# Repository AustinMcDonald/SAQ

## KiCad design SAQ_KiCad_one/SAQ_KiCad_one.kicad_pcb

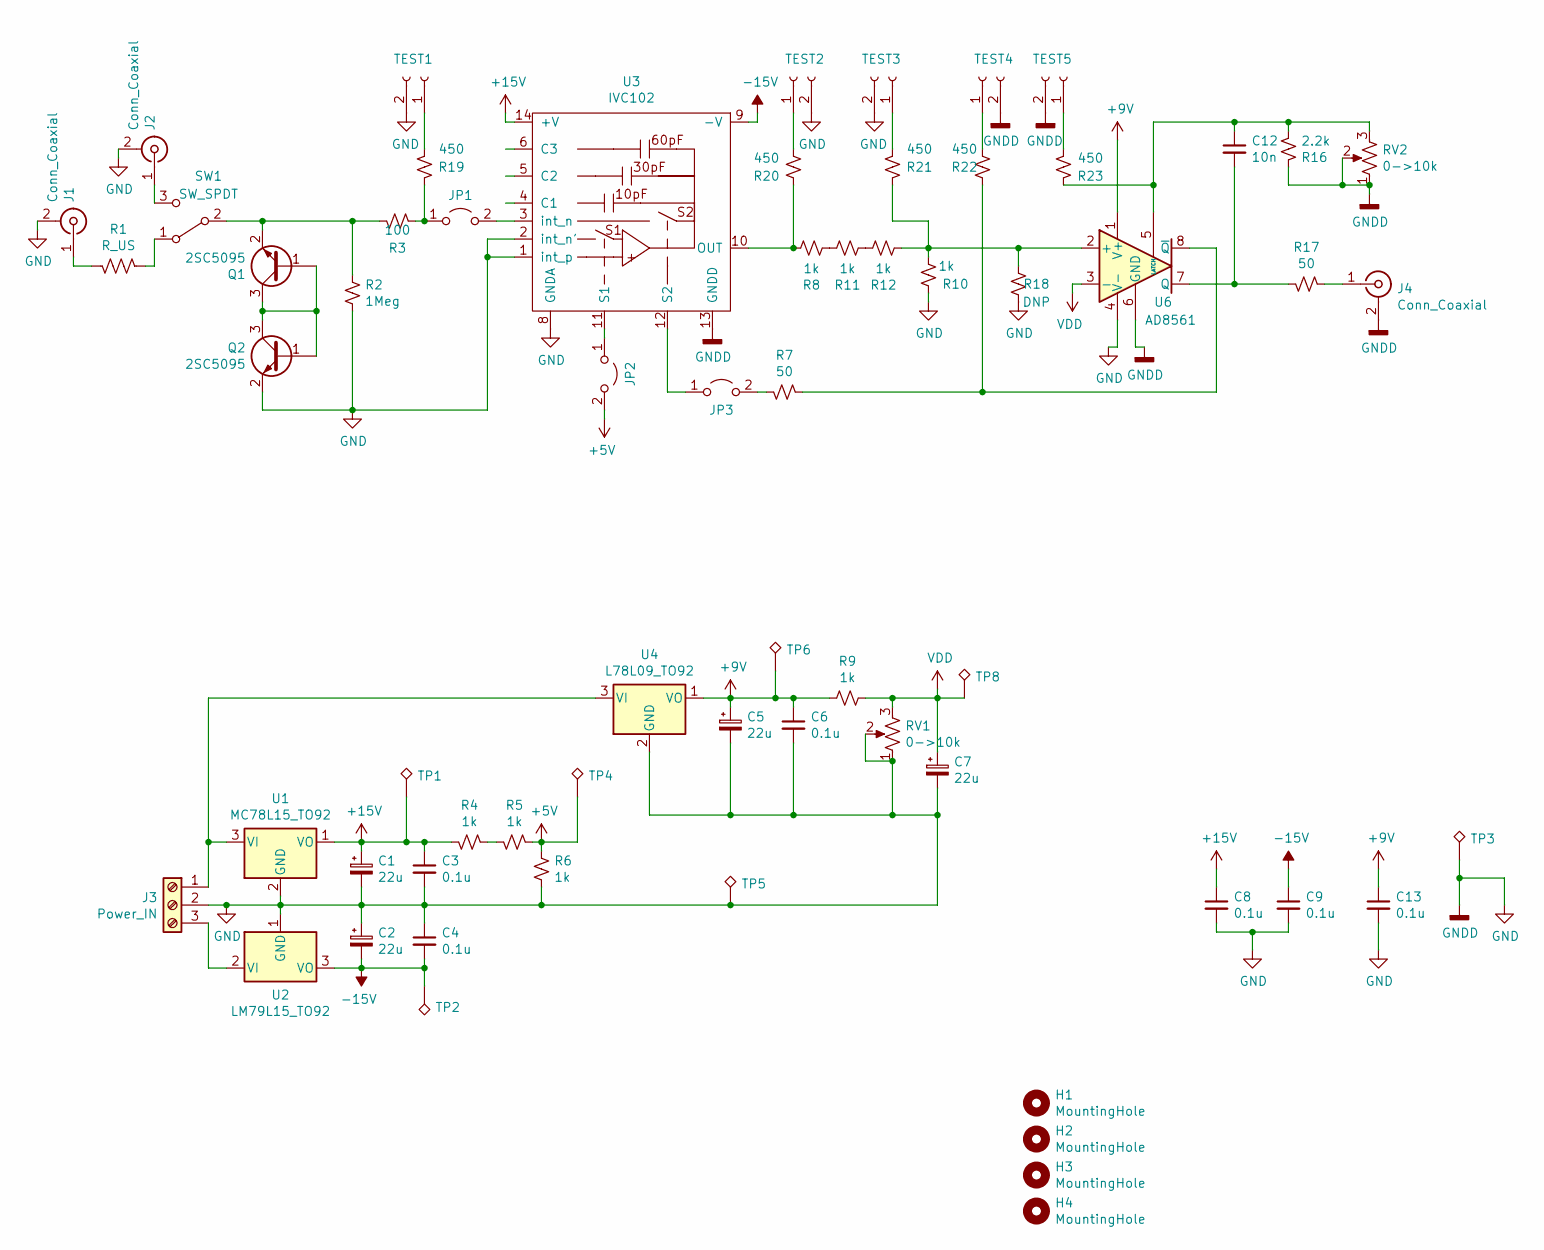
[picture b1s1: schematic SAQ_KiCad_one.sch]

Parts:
C1, C2, C5, C7: 22u; CP_Elec_5x5.3
C3, C4, C6, C8, C9, C13: 0.1u; C_1206_3216Metric_Pad1.33x1.80mm_HandSolder
C12: 10n; C_1206_3216Metric_Pad1.33x1.80mm_HandSolder
H1, H2, H3, H4: MountingHole; MountingHole_3.2mm_M3_DIN965
J1, J2, J4: Conn_Coaxial; SMA_Amphenol_132134_Vertical
J3: Power_IN; TerminalBlock_MetzConnect_Type055_RT01503HDWU_1x03_P5.00mm_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
JP1: Jumper_2_Open; R_Axial_DIN0204_L3.6mm_D1.6mm_P2.54mm_Vertical
JP2, JP3: Jumper_2_Open; SolderJumper-2_P1.3mm_Open_RoundedPad1.0x1.5mm
Q1, Q2: 2SC5095; SOT-23
R1: R_US; R_Axial_DIN0204_L3.6mm_D1.6mm_P7.62mm_Horizontal
R2: 1Meg; R_0805_2012Metric_Pad1.20x1.40mm_HandSolder
R3: 100; R_0805_2012Metric_Pad1.20x1.40mm_HandSolder
R4, R5, R6, R8, R9, R10, R11, R12: 1k; R_0805_2012Metric_Pad1.20x1.40mm_HandSolder
R7, R17: 50; R_0805_2012Metric_Pad1.20x1.40mm_HandSolder
R16: 2.2k; R_0805_2012Metric_Pad1.20x1.40mm_HandSolder
R18: DNP; R_0805_2012Metric_Pad1.20x1.40mm_HandSolder
R19, R20, R21, R22, R23: 450; R_0805_2012Metric_Pad1.20x1.40mm_HandSolder
RV1, RV2: 0->10k; Potentiometer_Bourns_3214W_Vertical
SW1: SW_SPDT; SW_Slide_1P2T_CK_OS102011MS2Q
TEST1, TEST2, TEST3, TEST4, TEST5: Conn_01x02_Female; PinSocket_1x02_P2.54mm_Vertical
TP1, TP2, TP4, TP6, TP8: TestPoint_Alt; TestPoint_THTPad_2.5x2.5mm_Drill1.2mm
TP3, TP5: TestPoint_Alt; TestPoint_THTPad_D4.0mm_Drill2.0mm
U1: MC78L15_TO92; TO-92_Inline
U2: LM79L15_TO92; TO-92_Inline
U3: IVC102; SOIC-14_3.9x8.7mm_P1.27mm
U4: L78L09_TO92; TO-92_Inline
U6: AD8561; SOIC-8_3.9x4.9mm_P1.27mm

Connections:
+5V: JP2.2 (B), R5.2, R6.1, TP4.1
+9V: C5.1, C6.1, C13.1, R9.2, TP6.1, U4.1 (VO), U6.1 (V+)
+15V: C1.1, C3.1, C8.1, R4.1, TP1.1, U1.1 (VO), U3.14 (+V)
-15V: C2.2, C4.2, C9.1, TP2.1, U2.3 (VO), U3.9 (-V)
GND: C1.2, C2.1, C3.2, C4.1, C5.2, C6.2, C7.2, C8.2, C9.2, C13.2, J1.2 (Ext), J2.2 (Ext), J3.2, J4.2 (Ext), Q2.2 (E), R2.1, R6.2, R10.1, R16.2, R18.2, RV1.1, RV1.2, RV2.1, RV2.2, TEST1.2, TEST2.2, TEST3.2, TEST4.2, TEST5.2, TP3.1, TP5.1, U1.2 (GND), U2.1 (GND), U3.1 (int_p), U3.2 (int_n'), U3.7 (nc), U3.8 (GNDA), U3.13 (GNDD), U4.2 (GND), U6.4 (V-), U6.6 (GND)
unnamed: C12.1, R16.1, R23.2, RV2.3, U6.5 (LATCH)
unnamed: C12.2, R17.1, U6.7 (Q)
unnamed: J1.1 (In), R1.2
unnamed: J2.1 (In), SW1.3 (C)
unnamed: J3.1, U1.3 (VI), U4.3 (VI)
unnamed: J3.3, U2.2 (VI)
unnamed: J4.1 (In), R17.2
unnamed: JP1.1 (A), R3.2, R19.2
unnamed: JP1.2 (B), U3.3 (int_n)
unnamed: JP2.1 (A), U3.11 (S1)
unnamed: JP3.1 (A), U3.12 (S2)
unnamed: JP3.2 (B), R7.1
unnamed: Q1.1 (B), Q1.3 (C), Q2.1 (B), Q2.3 (C)
unnamed: Q1.2 (E), R2.2, R3.1, SW1.2 (B)
unnamed: R1.1, SW1.1 (A)
unnamed: R4.2, R5.1
unnamed: R10.2, R12.2, R18.1, R21.2, U6.2 (+)
unnamed: R8.2, R11.1
unnamed: R11.2, R12.1
unnamed: R19.1, TEST1.1
unnamed: R20.1, TEST2.1
unnamed: R8.1, R20.2, U3.10 (OUT)
unnamed: R21.1, TEST3.1
unnamed: R22.1, TEST4.1
unnamed: R7.2, R22.2, U6.8 (~Q)
unnamed: R23.1, TEST5.1
VDD: C7.1, R9.1, RV1.3, TP8.1, U6.3 (-)

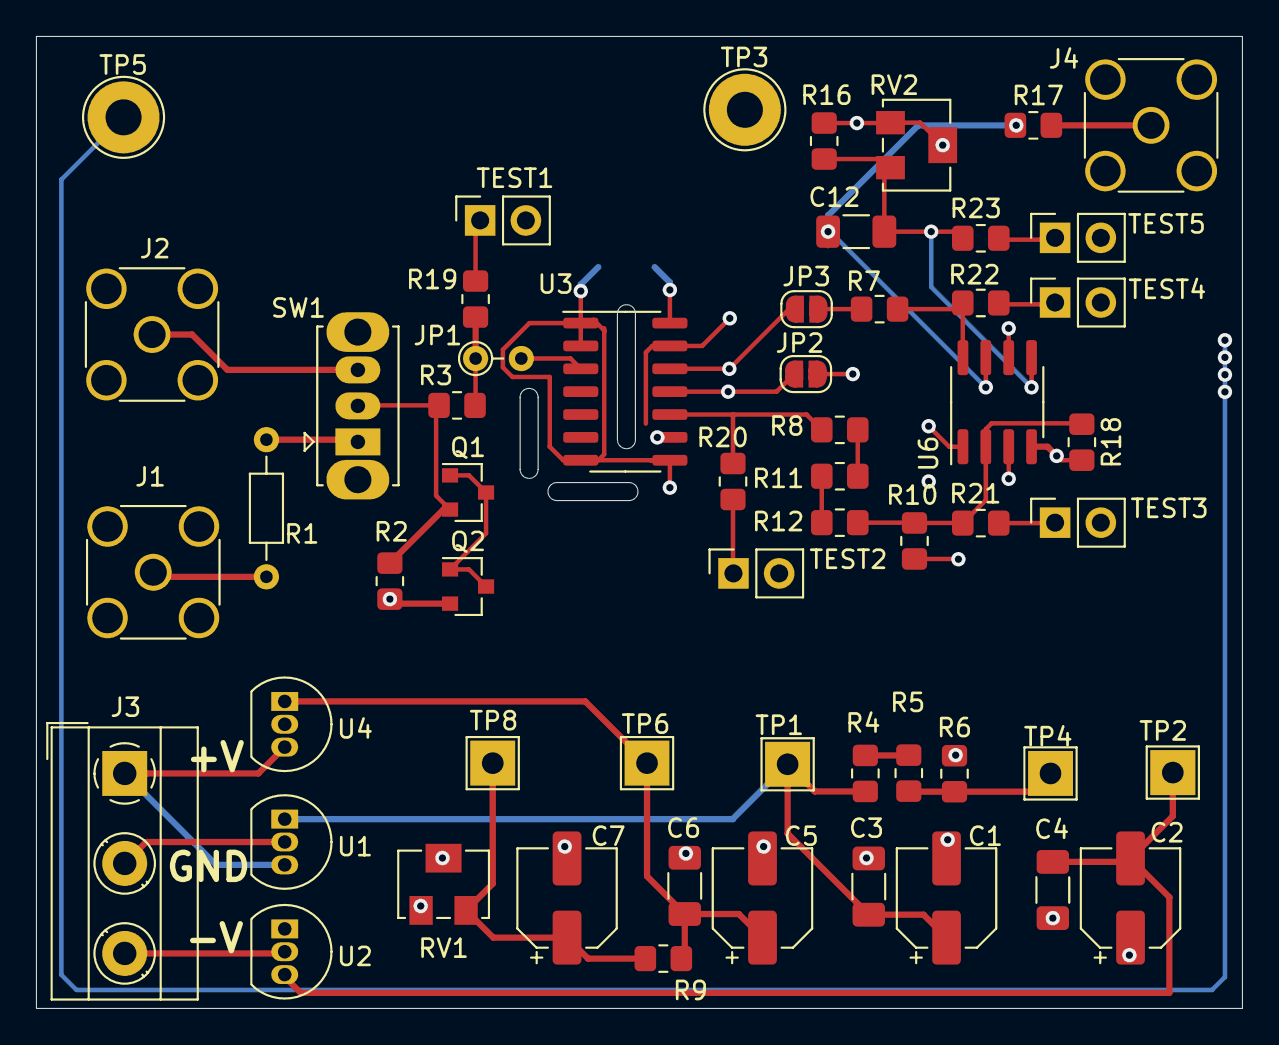
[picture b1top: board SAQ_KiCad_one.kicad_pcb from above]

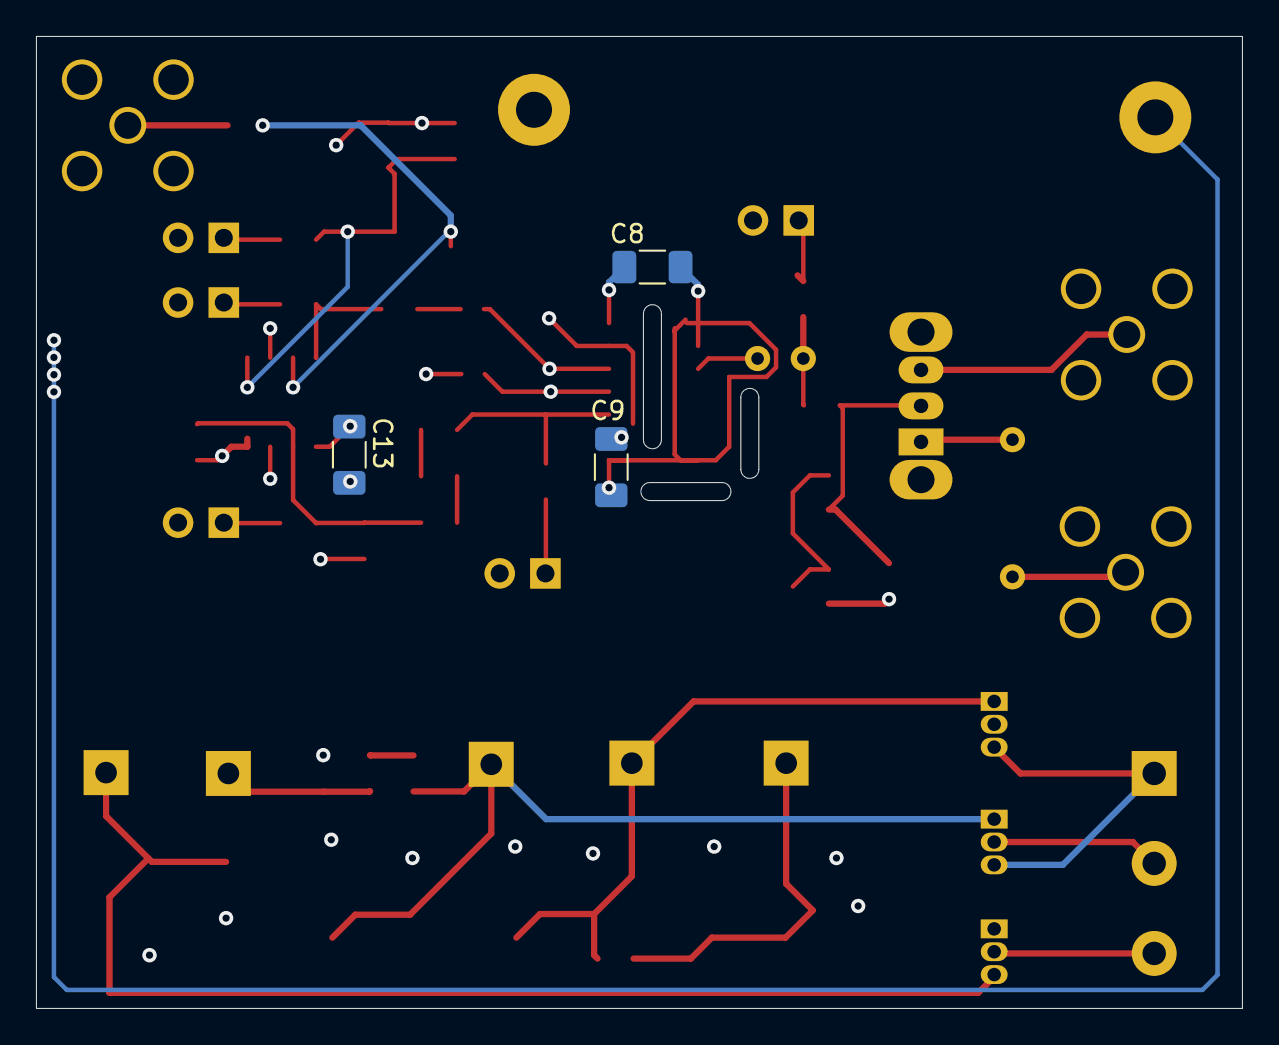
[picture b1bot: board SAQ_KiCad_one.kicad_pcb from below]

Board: 4 copper layers, 67.0 x 54.0 mm, 60 parts (3 on the bottom side), 32 nets.

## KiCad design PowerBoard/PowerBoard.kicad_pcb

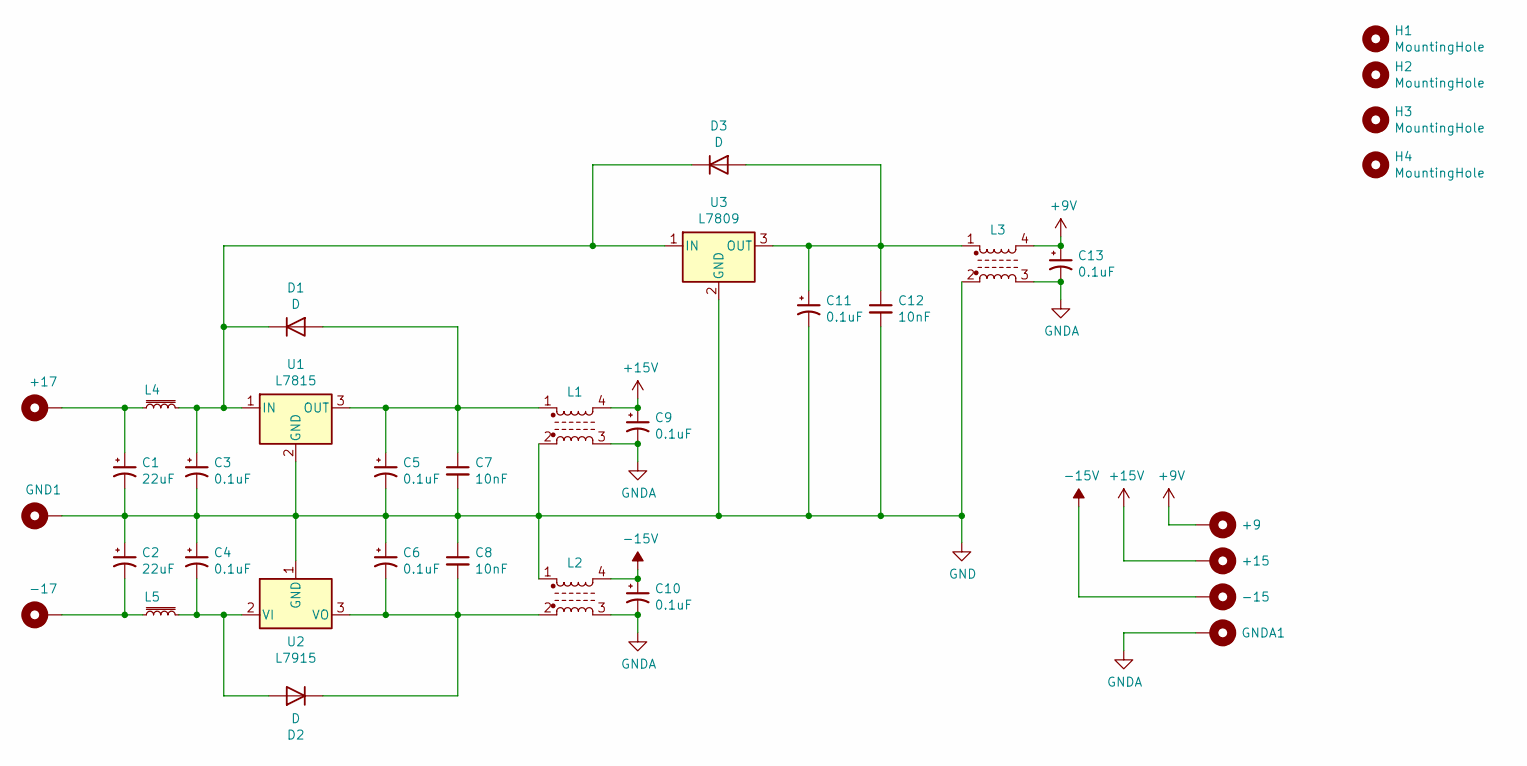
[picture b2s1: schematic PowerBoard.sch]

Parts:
+9, +15, +17: MountingHole_Pad; MountingHole_2.2mm_M2_DIN965_Pad
-15, -17: MountingHole_Pad; MountingHole_2.2mm_M2_DIN965_Pad
C1, C2: 22uF; CP_Elec_6.3x5.3
C3, C4, C5, C6, C9, C10, C11, C13: 0.1uF; C_1206_3216Metric_Pad1.33x1.80mm_HandSolder
C7, C8, C12: 10nF; C_1206_3216Metric_Pad1.33x1.80mm_HandSolder
D1, D2, D3: D; D_SMA_Handsoldering
GND1: MountingHole_Pad; MountingHole_2.2mm_M2_DIN965_Pad
GNDA1: MountingHole_Pad; MountingHole_2.2mm_M2_DIN965_Pad
H1, H2, H3, H4: MountingHole; MountingHole_3.2mm_M3
L1, L2, L3: L_Core_Ferrite_Coupled_1423; Filter_Bourns_SRF0905_6.0x9.2mm
L4, L5: L_Core_Iron_Small; L_Bourns_SRP5030T
U1: L7815; TO-252-2
U2: L7915; TO-252-2
U3: L7809; TO-252-2

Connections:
+9V: +9.1, C13.1, L3.4
+15V: +15.1, C9.1, L1.4
-15V: -15.1, C10.1, L2.4
GND: C1.2, C2.1, C3.2, C4.1, C5.2, C6.1, C7.2, C8.1, C11.2, C12.2, GND1.1, L1.2, L2.1, L3.2, U1.2 (GND), U2.1 (GND), U3.2 (GND); also elsewhere on the board
GNDA: C9.2, C10.2, C13.2, GNDA1.1, L1.3, L2.3, L3.3; also elsewhere on the board
unnamed: +17.1, C1.1, L4.1
unnamed: -17.1, C2.2, L5.1
unnamed: C3.1, D1.1 (K), D3.1 (K), L4.2, U1.1 (IN), U3.1 (IN)
unnamed: C4.2, D2.2 (A), L5.2, U2.2 (VI)
unnamed: C5.1, C7.1, D1.2 (A), L1.1, U1.3 (OUT)
unnamed: C6.2, C8.2, D2.1 (K), L2.2, U2.3 (VO)
unnamed: C11.1, C12.1, D3.2 (A), L3.1, U3.3 (OUT)

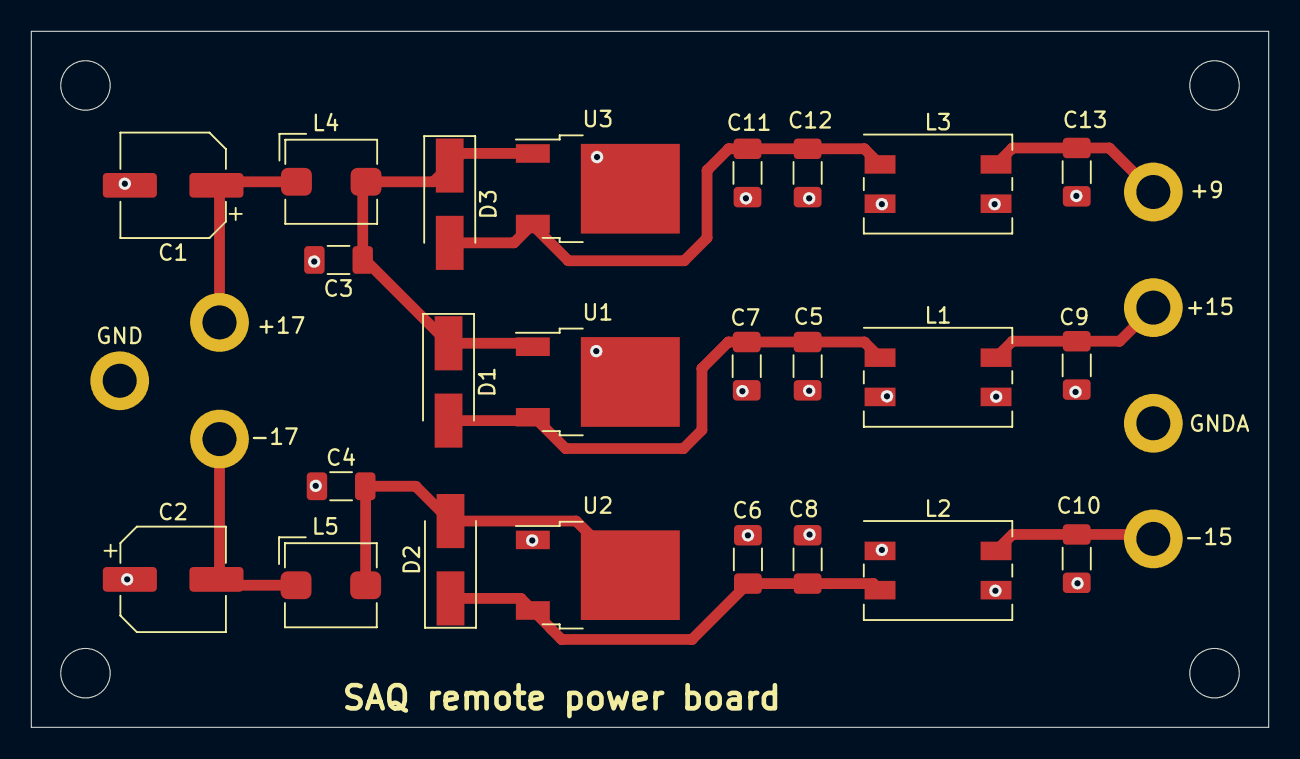
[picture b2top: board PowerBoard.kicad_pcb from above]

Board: 2 copper layers, 80.0 x 45.0 mm, 35 parts (0 on the bottom side), 12 nets.

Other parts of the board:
GND: MountingHole_Pad; MountingHole_2.2mm_M2_DIN965_Pad
GNDA: MountingHole_Pad; MountingHole_2.2mm_M2_DIN965_Pad

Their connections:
GND: GND.1; also elsewhere on the board
GNDA: GNDA.1; also elsewhere on the board

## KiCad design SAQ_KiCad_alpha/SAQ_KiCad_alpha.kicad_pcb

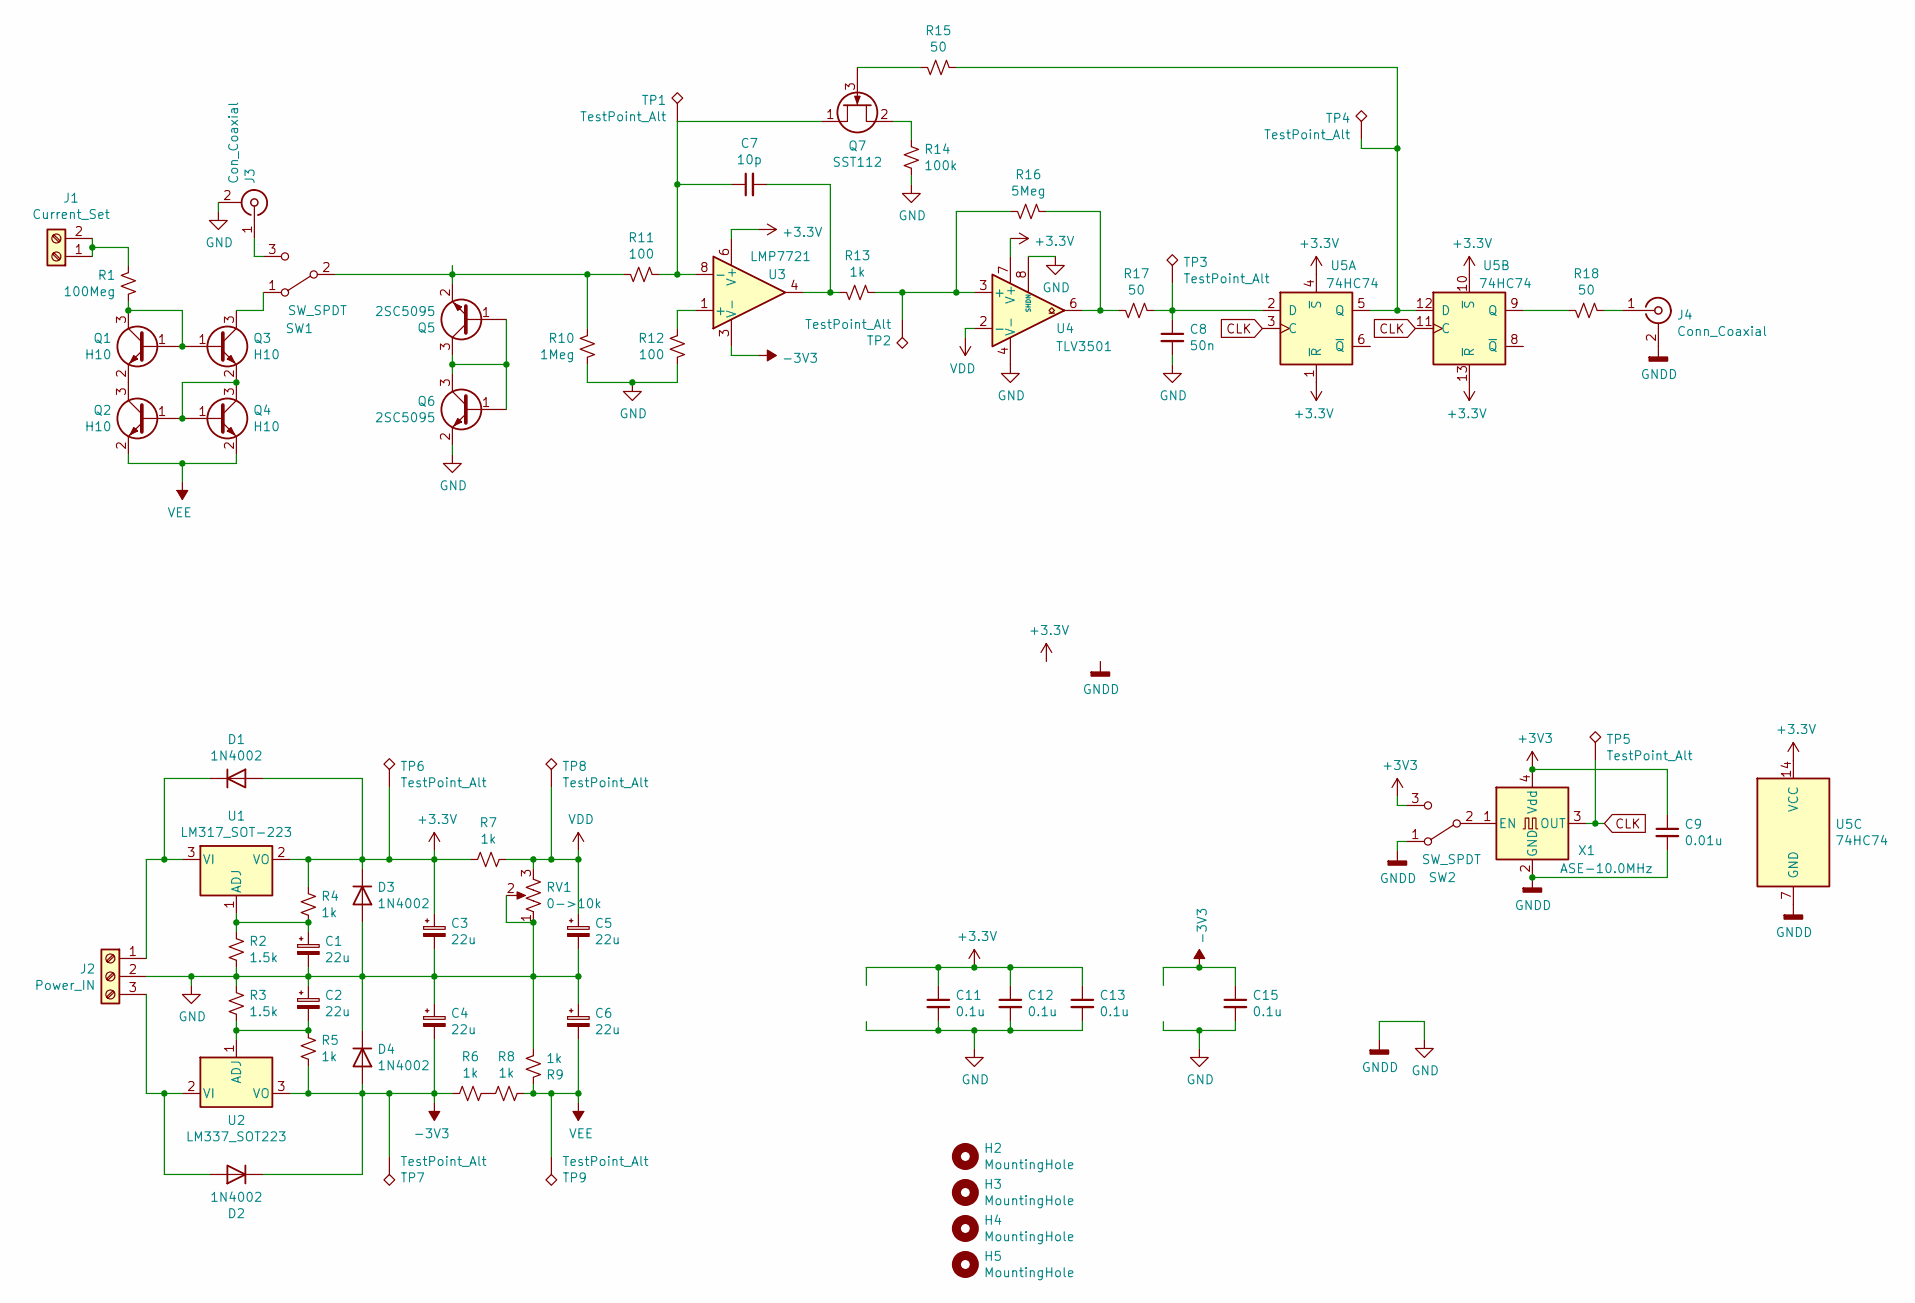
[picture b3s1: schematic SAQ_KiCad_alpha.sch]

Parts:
C1, C2, C3, C4, C5, C6: 22u; CP_Elec_5x5.3
C7: 10p; C_1206_3216Metric_Pad1.33x1.80mm_HandSolder
C8: 50n; C_1206_3216Metric_Pad1.33x1.80mm_HandSolder
C9: 0.01u; C_1206_3216Metric_Pad1.33x1.80mm_HandSolder
C11, C12, C13, C15: 0.1u; C_1206_3216Metric_Pad1.33x1.80mm_HandSolder
D1, D2, D3, D4: 1N4002; D_DO-41_SOD81_P10.16mm_Horizontal
H2, H3, H4, H5: MountingHole; MountingHole_3.2mm_M3_DIN965
J1: Current_Set; TerminalBlock_MetzConnect_Type011_RT05502HBWC_1x02_P5.00mm_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
J2: Power_IN; TerminalBlock_MetzConnect_Type055_RT01503HDWU_1x03_P5.00mm_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
J3: Con_Coaxial; SMA_Amphenol_132134_Vertical
J4: Conn_Coaxial; SMA_Amphenol_132134_Vertical
Q1, Q2, Q3, Q4: H10; SOT-23
Q5, Q6: 2SC5095; SOT-23
Q7: SST112; SOT-23
R1: 100Meg; R_0805_2012Metric_Pad1.20x1.40mm_HandSolder
R2, R3: 1.5k; R_0805_2012Metric_Pad1.20x1.40mm_HandSolder
R4, R5, R6, R7, R8, R9, R13: 1k; R_0805_2012Metric_Pad1.20x1.40mm_HandSolder
R10: 1Meg; R_0805_2012Metric_Pad1.20x1.40mm_HandSolder
R11, R12: 100; R_0805_2012Metric_Pad1.20x1.40mm_HandSolder
R14: 100k; R_0805_2012Metric_Pad1.20x1.40mm_HandSolder
R15, R17, R18: 50; R_0805_2012Metric_Pad1.20x1.40mm_HandSolder
R16: 5Meg; R_0805_2012Metric_Pad1.20x1.40mm_HandSolder
RV1: 0->10k; Potentiometer_Bourns_3214W_Vertical
SW1, SW2: SW_SPDT; SW_Slide_1P2T_CK_OS102011MS2Q
TP1, TP2, TP3, TP4, TP5, TP6, TP7, TP8, TP9: TestPoint_Alt; TestPoint_THTPad_1.0x1.0mm_Drill0.5mm
U1: LM317_SOT-223; SOT-223-3_TabPin2
U2: LM337_SOT223; SOT-223-3_TabPin2
U3: LMP7721; SOIC-8_3.9x4.9mm_P1.27mm
U4: TLV3501; SOIC-8_3.9x4.9mm_P1.27mm
U5: 74HC74; SOIC-14_3.9x8.7mm_P1.27mm
X1: ASE-10.0MHz; Oscillator_SMD_Abracon_ASE-4Pin_3.2x2.5mm

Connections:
-3V3: C4.2, C15.1, D2.1 (K), D4.2 (A), R5.2, R6.2, TP7.1, U2.3 (VO), U3.3 (V-)
CLK: TP5.1, U5.3 (C), U5.11 (C), X1.3 (OUT)
GND: C1.2, C2.1, C3.2, C4.1, C5.2, C6.1, C8.2, C9.2, C11.2, C12.2, C13.2, C15.2, D3.2 (A), D4.1 (K), J2.2, J3.2 (Ext), J4.2 (Ext), Q6.2 (E), R2.2, R3.1, R9.1, R10.1, R12.1, R14.1, RV1.1, RV1.2, SW2.1 (A), U4.4 (V-), U4.8 (SHDN), U5.7 (GND), X1.2 (GND)
unnamed: C1.1, R2.1, R4.2, U1.1 (ADJ)
unnamed: C2.2, R3.2, R5.1, U2.1 (ADJ)
unnamed: C7.1, Q7.1 (D), R11.2, TP1.1, U3.8 (-)
unnamed: C7.2, R13.1, U3.4
unnamed: C8.1, R17.2, TP3.1, U5.2 (D)
unnamed: D1.1 (K), J2.1, U1.3 (VI)
unnamed: D2.2 (A), J2.3, U2.2 (VI)
unnamed: J1.1, J1.2, R1.2
unnamed: J3.1 (In), SW1.3 (C)
unnamed: J4.1 (In), R18.2
unnamed: Q1.1 (B), Q1.3 (C), Q3.1 (B), R1.1
unnamed: Q1.2 (E), Q2.3 (C)
unnamed: Q2.1 (B), Q3.2 (E), Q4.1 (B), Q4.3 (C)
unnamed: Q3.3 (C), SW1.1 (A)
unnamed: Q5.1 (B), Q5.3 (C), Q6.1 (B), Q6.3 (C)
unnamed: Q5.2 (E), R10.2, R11.1, SW1.2 (B)
unnamed: Q7.2 (S), R14.2
unnamed: Q7.3 (G), R15.1
unnamed: R6.1, R8.2
unnamed: R12.2, U3.1 (+)
unnamed: R13.2, R16.1, TP2.1, U4.3 (+)
unnamed: R15.2, TP4.1, U5.5 (Q), U5.12 (D)
unnamed: R16.2, R17.1, U4.6
unnamed: R18.1, U5.9 (Q)
unnamed: SW2.2 (B), X1.1 (EN)
VDD: C5.1, R7.1, RV1.3, TP8.1, U4.2 (-)
VEE: C6.2, Q2.2 (E), Q4.2 (E), R8.1, R9.2, TP9.1

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
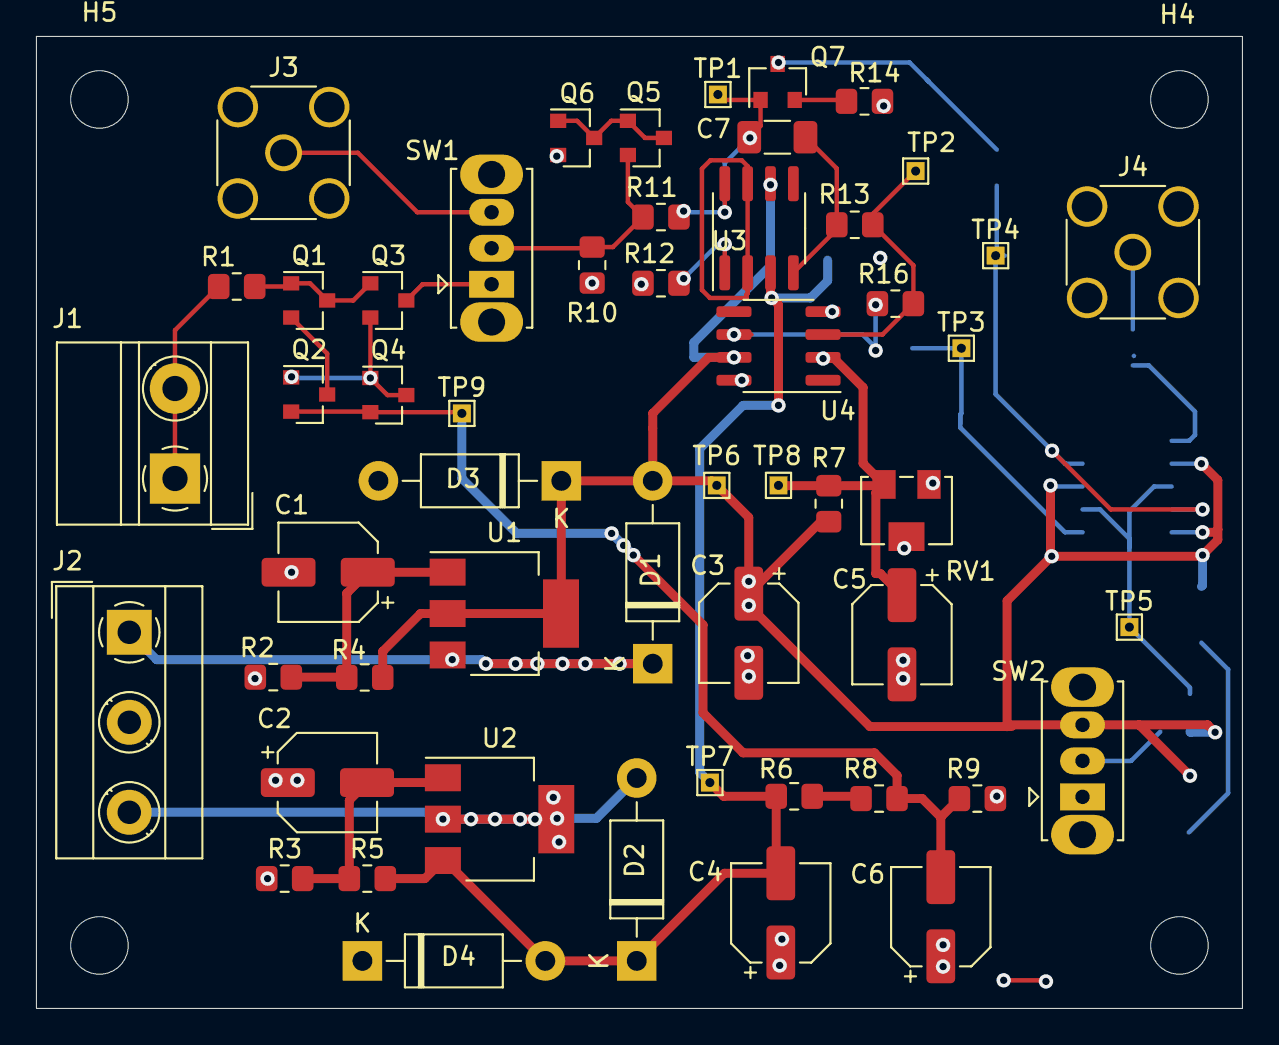
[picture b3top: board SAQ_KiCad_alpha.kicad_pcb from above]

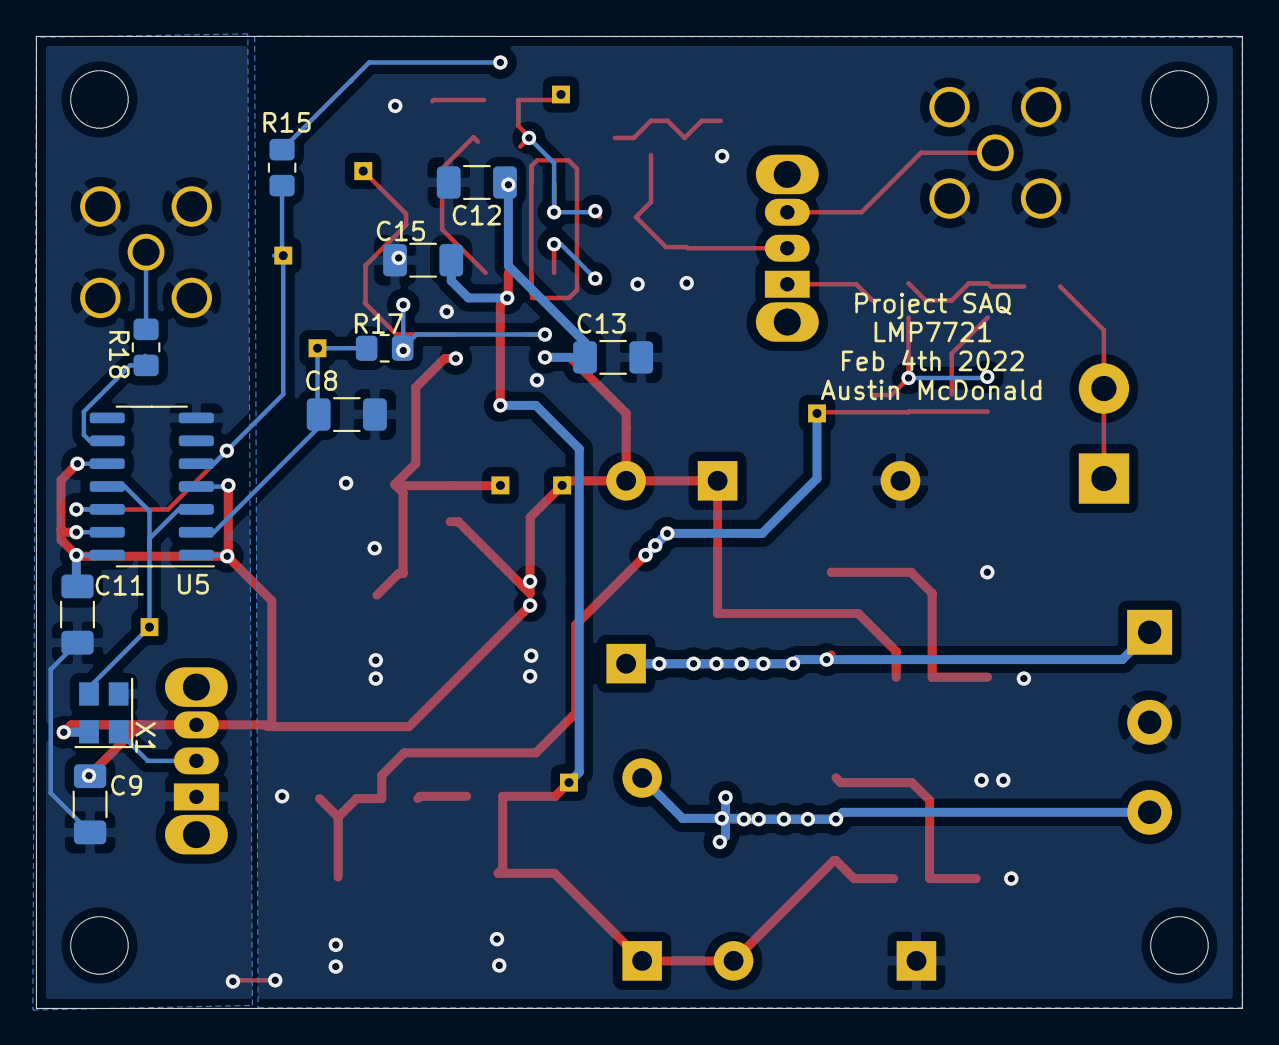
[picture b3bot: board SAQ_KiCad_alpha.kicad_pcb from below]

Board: 2 copper layers, 67.0 x 54.0 mm, 68 parts (11 on the bottom side), 31 nets.

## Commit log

2022-02-16 first
2022-03-08 added pdf
2022-04-22 updated IVC board
2022-04-25 finised second version
2022-05-02 added changes to one and made a remote power board
2022-05-09 latest
